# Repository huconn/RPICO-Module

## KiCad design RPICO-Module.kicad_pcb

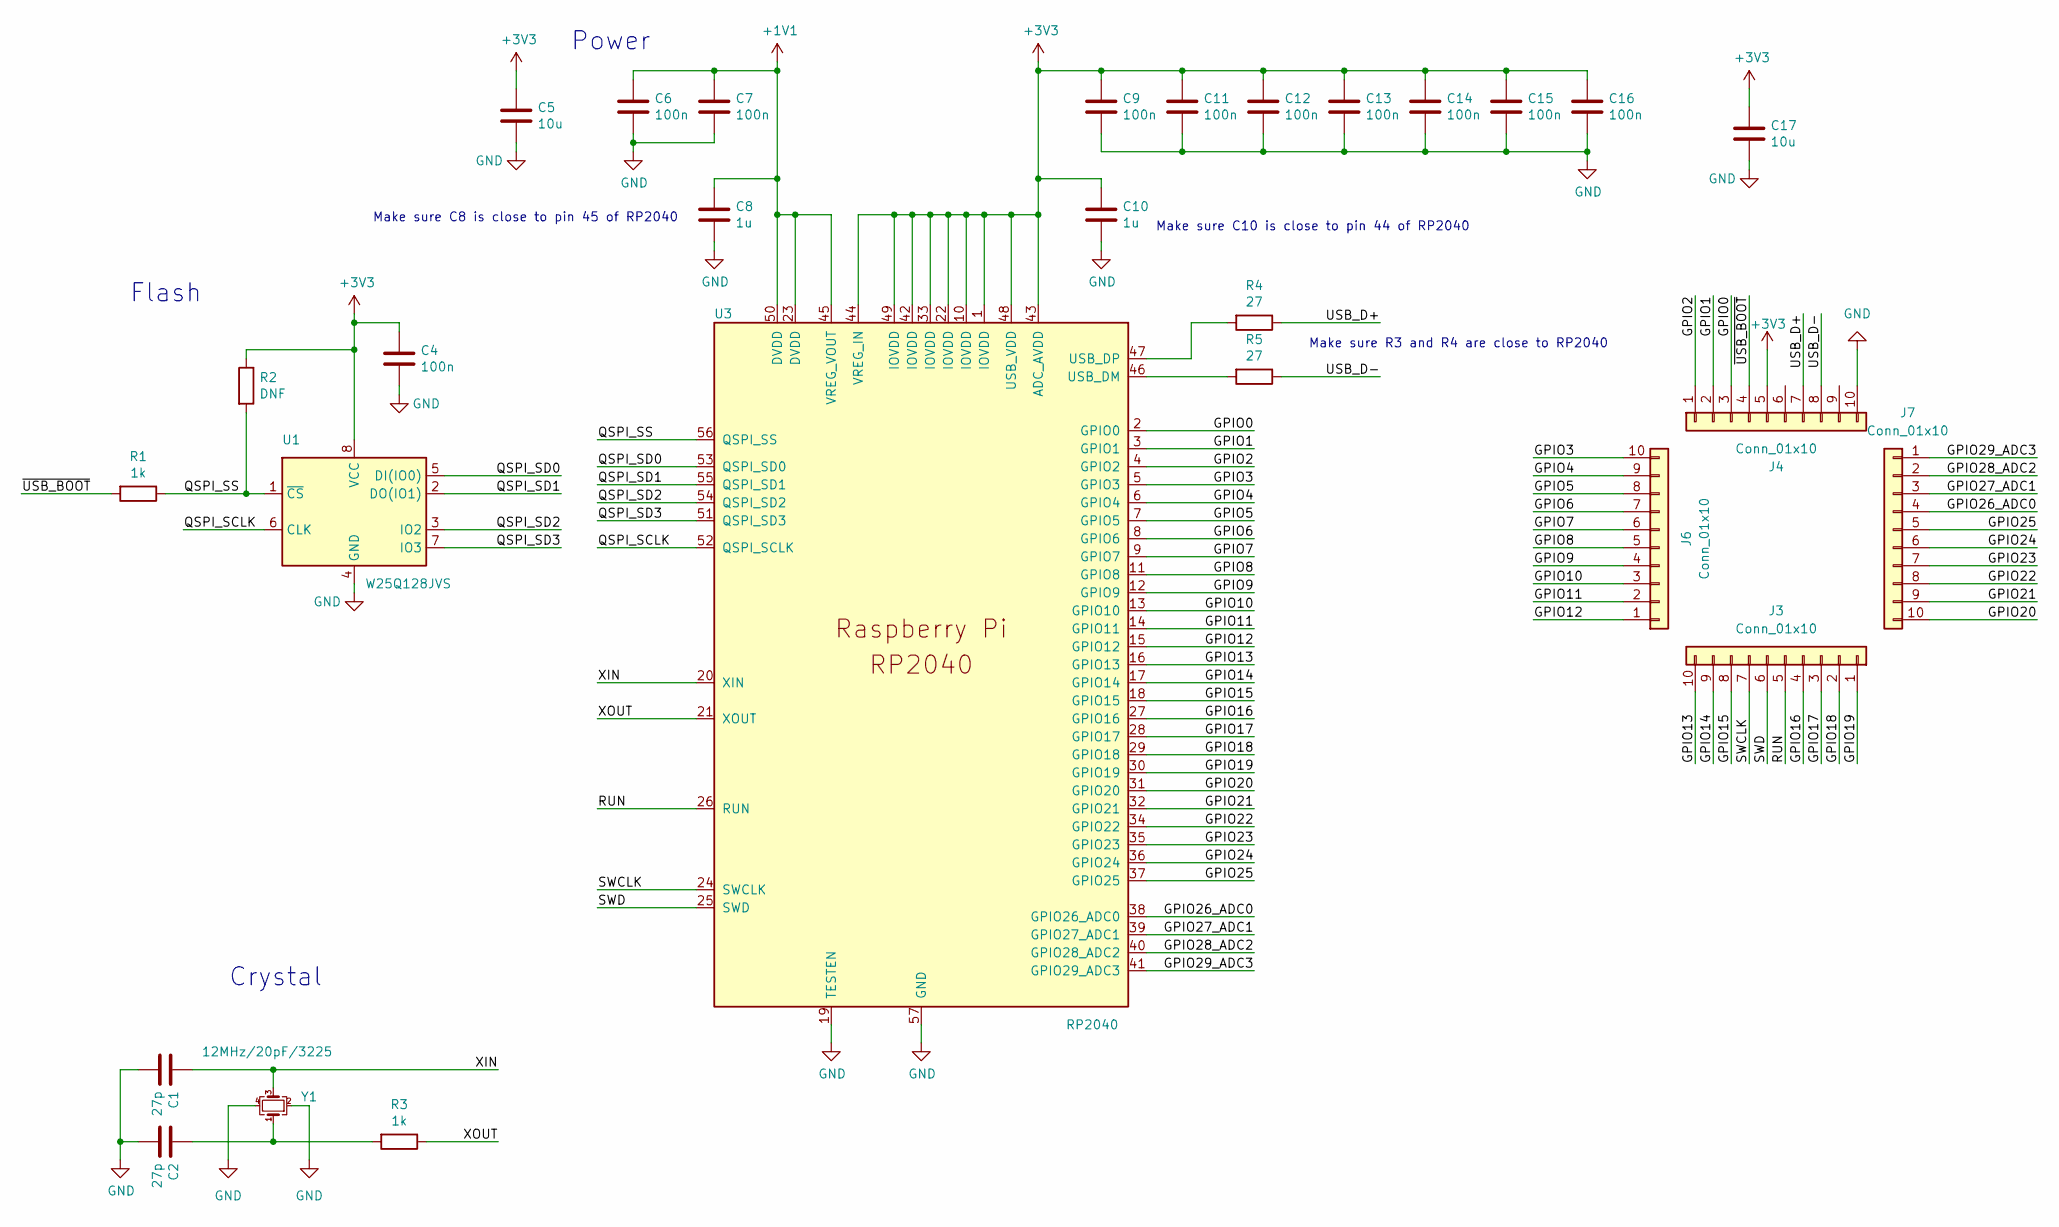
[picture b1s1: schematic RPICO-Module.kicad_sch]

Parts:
C1, C2: 27p; C_0603_1608Metric; LCSC C1656
C4, C6, C7, C9, C11, C12, C13, C14, C15, C16: 100n; C_0603_1608Metric; LCSC C14663
C5, C17: 10u; C_0805_2012Metric; LCSC C19702
C8, C10: 1u; C_0603_1608Metric; LCSC C15849
J3, J4, J6, J7: Conn_01x10; PinHeader_1x10_P2.00mm_Vertical
R1, R3: 1k; C_0603_1608Metric; LCSC C21190
R2: DNF; C_0603_1608Metric
R4, R5: 27; C_0603_1608Metric; LCSC C25190
U1: W25Q128JVS; SOIC-8_5.23x5.23mm_P1.27mm; LCSC C97521
U3: RP2040; RP2040-QFN-56; LCSC C2040
Y1: 12MHz/20pF/3225; Crystal_SMD_3225-4Pin_3.2x2.5mm; LCSC C9002

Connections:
+1V1: C6.1, C7.1, C8.1, U3.23 (DVDD), U3.45 (VREG_VOUT), U3.50 (DVDD)
+3V3: C4.1, C5.1, C9.1, C10.1, C11.1, C12.1, C13.1, C14.1, C15.1, C16.1, C17.1, J4.5, R2.1, U1.8 (VCC), U3.1 (IOVDD), U3.10 (IOVDD), U3.22 (IOVDD), U3.33 (IOVDD), U3.42 (IOVDD), U3.43 (ADC_AVDD), U3.44 (VREG_IN), U3.48 (USB_VDD), U3.49 (IOVDD)
/GPIO0: J4.3, U3.2 (GPIO0)
/GPIO1: J4.2, U3.3 (GPIO1)
/GPIO2: J4.1, U3.4 (GPIO2)
/GPIO3: J6.10, U3.5 (GPIO3)
/GPIO4: J6.9, U3.6 (GPIO4)
/GPIO5: J6.8, U3.7 (GPIO5)
/GPIO6: J6.7, U3.8 (GPIO6)
/GPIO7: J6.6, U3.9 (GPIO7)
/GPIO8: J6.5, U3.11 (GPIO8)
/GPIO9: J6.4, U3.12 (GPIO9)
/GPIO10: J6.3, U3.13 (GPIO10)
/GPIO11: J6.2, U3.14 (GPIO11)
/GPIO12: J6.1, U3.15 (GPIO12)
/GPIO13: J3.10, U3.16 (GPIO13)
/GPIO14: J3.9, U3.17 (GPIO14)
/GPIO15: J3.8, U3.18 (GPIO15)
/GPIO16: J3.4, U3.27 (GPIO16)
/GPIO17: J3.3, U3.28 (GPIO17)
/GPIO18: J3.2, U3.29 (GPIO18)
/GPIO19: J3.1, U3.30 (GPIO19)
/GPIO20: J7.10, U3.31 (GPIO20)
/GPIO21: J7.9, U3.32 (GPIO21)
/GPIO22: J7.8, U3.34 (GPIO22)
/GPIO23: J7.7, U3.35 (GPIO23)
/GPIO24: J7.6, U3.36 (GPIO24)
/GPIO25: J7.5, U3.37 (GPIO25)
/GPIO26_ADC0: J7.4, U3.38 (GPIO26_ADC0)
/GPIO27_ADC1: J7.3, U3.39 (GPIO27_ADC1)
/GPIO28_ADC2: J7.2, U3.40 (GPIO28_ADC2)
/GPIO29_ADC3: J7.1, U3.41 (GPIO29_ADC3)
/QSPI_SCLK: U1.6 (CLK), U3.52 (QSPI_SCLK)
/QSPI_SD0: U1.5 (DI(IO0)), U3.53 (QSPI_SD0)
/QSPI_SD1: U1.2 (DO(IO1)), U3.55 (QSPI_SD1)
/QSPI_SD2: U1.3 (IO2), U3.54 (QSPI_SD2)
/QSPI_SD3: U1.7 (IO3), U3.51 (QSPI_SD3)
/QSPI_SS: R1.1, R2.2, U1.1 (~CS), U3.56 (QSPI_SS)
/RUN: J3.5, U3.26 (RUN)
/SWCLK: J3.7, U3.24 (SWCLK)
/SWD: J3.6, U3.25 (SWD)
/USB_D+: J4.7, R4.1
/USB_D-: J4.8, R5.1
/XIN: C1.1, U3.20 (XIN), Y1.3
/XOUT: R3.1, U3.21 (XOUT)
/~USB_BOOT: J4.4, R1.2
GND: C1.2, C2.2, C4.2, C5.2, C6.2, C7.2, C8.2, C9.2, C10.2, C11.2, C12.2, C13.2, C14.2, C15.2, C16.2, C17.2, J4.10, U1.4 (GND), U3.19 (TESTEN), U3.57 (GND), Y1.2, Y1.4
unnamed: C2.1, R3.2, Y1.1
unnamed: R4.2, U3.47 (USB_DP)
unnamed: R5.2, U3.46 (USB_DM)

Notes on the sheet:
Flash
Crystal
Make sure C8 is close to pin 45 of RP2040
Power
Make sure C10 is close to pin 44 of RP2040
Make sure R3 and R4 are close to RP2040

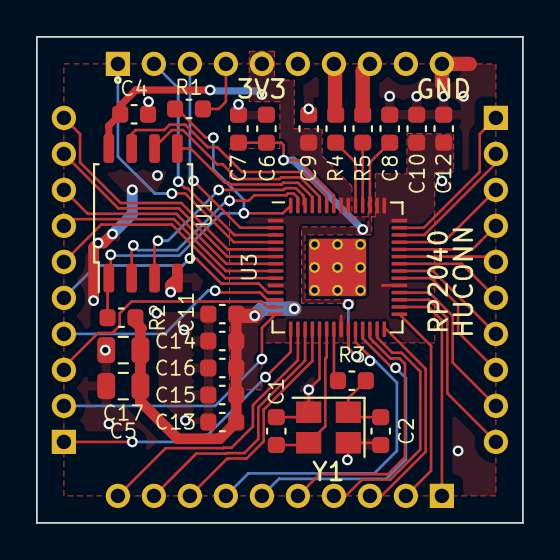
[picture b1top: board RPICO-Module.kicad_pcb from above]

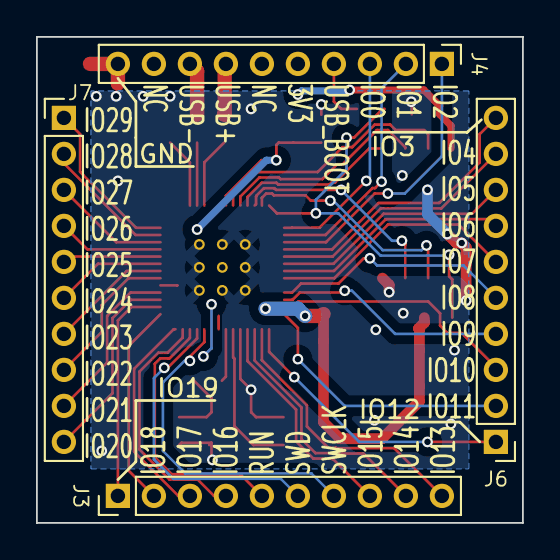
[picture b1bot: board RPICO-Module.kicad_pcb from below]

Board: 2 copper layers, 27.0 x 27.0 mm, 28 parts (4 on the bottom side), 50 nets.

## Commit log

2021-09-14 complete drawing schematic and artwork
